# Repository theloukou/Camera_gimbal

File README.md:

# 2-axis Camera Gimbal
Arduino-based 2-axis BLDC gimbal controller

This project consists the main study of my Thesis for my Bachelor of Science at the Department of Automation Engineering of the Piraeus University of Applied Sciences.

It is an Arduino Mega2560 based system, that consists of an extention PCB(shield) that acts as a motor driver for BLCD motors, and an interface between the Arduino and its peripheral devices (motor drivers, IMUs, switches, battery).
Microcontroller code is presented, as well as shield schematic/PCB layout/PCB Gerbers. Also, some 3D-Printed parts used around the gimbal frame are presented in STL form.

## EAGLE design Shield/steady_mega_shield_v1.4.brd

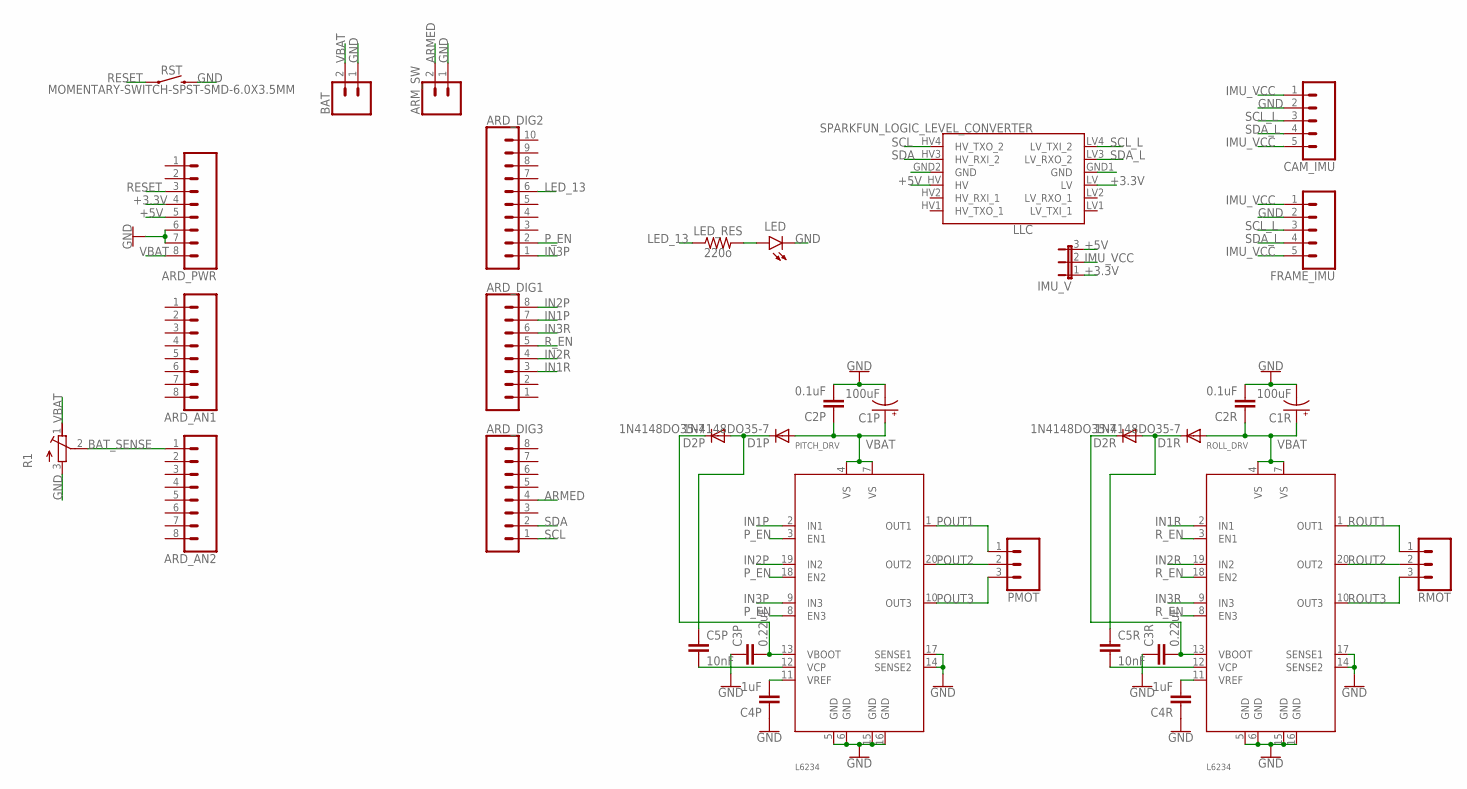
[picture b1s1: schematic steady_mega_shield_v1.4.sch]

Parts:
ARD_AN1, ARD_AN2: CONN_08"; 1X08
ARD_DIG1, ARD_DIG3: CONN_08"; 1X08
ARD_DIG2: CONN_10"; 1X10
ARD_PWR: CONN_08"; 1X08
ARM_SW: CONN_02; 1X02
BAT: CONN_02; 1X02
C1P, C1R: 100uF; CPOL-RADIAL-2.5MM-6.5MM
C2P, C2R: 0.1uF; C025-024X044
C3P, C3R: 0.22uF; C5B2.5
C4P, C4R: 1uF; C5B5.5
C5P, C5R: 10nF; C5B2.5
CAM_IMU: CONN_05JST; JST-5-PTH
D1P, D1R, D2P, D2R: 1N4148DO35-7; DO35-7
FRAME_IMU: CONN_05JST; JST-5-PTH
IMU_V: JP2E; JP2
LED: LED3MM; LED_3MM
LED_RES: 220o; 0805
LLC: SPARKFUN_LOGIC_LEVEL_CONVERTER
PITCH_DRV: L6234; DIL20
PMOT: CONN_03POLAR; MOLEX-1X3
R1: R-TRIMMT93XB; RTRIMT93XB
RMOT: CONN_03POLAR; MOLEX-1X3
ROLL_DRV: L6234; DIL20
RST: MOMENTARY-SWITCH-SPST-SMD-6.0X3.5MM; TACTILE_SWITCH_SMD_6.0X3.5MM

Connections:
+3.3V: ARD_PWR.4, IMU_V.1, LLC.LV
+5V: ARD_PWR.5, IMU_V.3, LLC.HV
ARMED: ARD_DIG3.4, ARM_SW.2
BAT_SENSE: ARD_AN2.1, R1.2 (S)
GND: ARD_PWR.6, ARD_PWR.7, ARM_SW.1, BAT.1, C1P.2 (-), C1R.2 (-), C2P.2, C2R.2, C3P.1, C3R.1, C4P.1, C4R.1, CAM_IMU.2, FRAME_IMU.2, LED.K (C), LLC.GND1 (GND), LLC.GND2 (GND), PITCH_DRV.5 (GND), PITCH_DRV.6 (GND), PITCH_DRV.14 (SENSE2), PITCH_DRV.15 (GND), PITCH_DRV.16 (GND), PITCH_DRV.17 (SENSE1), R1.3 (A), ROLL_DRV.5 (GND), ROLL_DRV.6 (GND), ROLL_DRV.14 (SENSE2), ROLL_DRV.15 (GND), ROLL_DRV.16 (GND), ROLL_DRV.17 (SENSE1), RST.2
IMU_VCC: CAM_IMU.1, CAM_IMU.5, FRAME_IMU.1, FRAME_IMU.5, IMU_V.2
IN1P: ARD_DIG1.7, PITCH_DRV.2 (IN1)
IN1R: ARD_DIG1.3, ROLL_DRV.2 (IN1)
IN2P: ARD_DIG1.8, PITCH_DRV.19 (IN2)
IN2R: ARD_DIG1.4, ROLL_DRV.19 (IN2)
IN3P: ARD_DIG2.1, PITCH_DRV.9 (IN3)
IN3R: ARD_DIG1.6, ROLL_DRV.9 (IN3)
LED_13: ARD_DIG2.6, LED_RES.1
unnamed: C4R.2, ROLL_DRV.11 (VREF)
unnamed: C4P.2, PITCH_DRV.11 (VREF)
unnamed: C5R.2, ROLL_DRV.12 (VCP)
unnamed: C3R.2, D2R.C, ROLL_DRV.13 (VBOOT)
unnamed: C5P.2, PITCH_DRV.12 (VCP)
unnamed: C3P.2, D2P.C, PITCH_DRV.13 (VBOOT)
unnamed: LED.A, LED_RES.2
unnamed: C5P.1, D1P.C, D2P.A
unnamed: C5R.1, D1R.C, D2R.A
POUT1: PITCH_DRV.1 (OUT1), PMOT.1
POUT2: PITCH_DRV.20 (OUT2), PMOT.2
POUT3: PITCH_DRV.10 (OUT3), PMOT.3
P_EN: ARD_DIG2.2, PITCH_DRV.3 (EN1), PITCH_DRV.8 (EN3), PITCH_DRV.18 (EN2)
RESET: ARD_PWR.3, RST.1
ROUT1: RMOT.1, ROLL_DRV.1 (OUT1)
ROUT2: RMOT.2, ROLL_DRV.20 (OUT2)
ROUT3: RMOT.3, ROLL_DRV.10 (OUT3)
R_EN: ARD_DIG1.5, ROLL_DRV.3 (EN1), ROLL_DRV.8 (EN3), ROLL_DRV.18 (EN2)
SCL: ARD_DIG3.1, LLC.HV4 (HV_TXO_2)
SCL_L: CAM_IMU.3, FRAME_IMU.3, LLC.LV4 (LV_TXI_2)
SDA: ARD_DIG3.2, LLC.HV3 (HV_RXI_2)
SDA_L: CAM_IMU.4, FRAME_IMU.4, LLC.LV3 (LV_RXO_2)
VBAT: ARD_PWR.8, BAT.2, C1P.1 (+), C1R.1 (+), C2P.1, C2R.1, D1P.A, D1R.A, PITCH_DRV.4 (VS), PITCH_DRV.7 (VS), R1.1 (E), ROLL_DRV.4 (VS), ROLL_DRV.7 (VS)

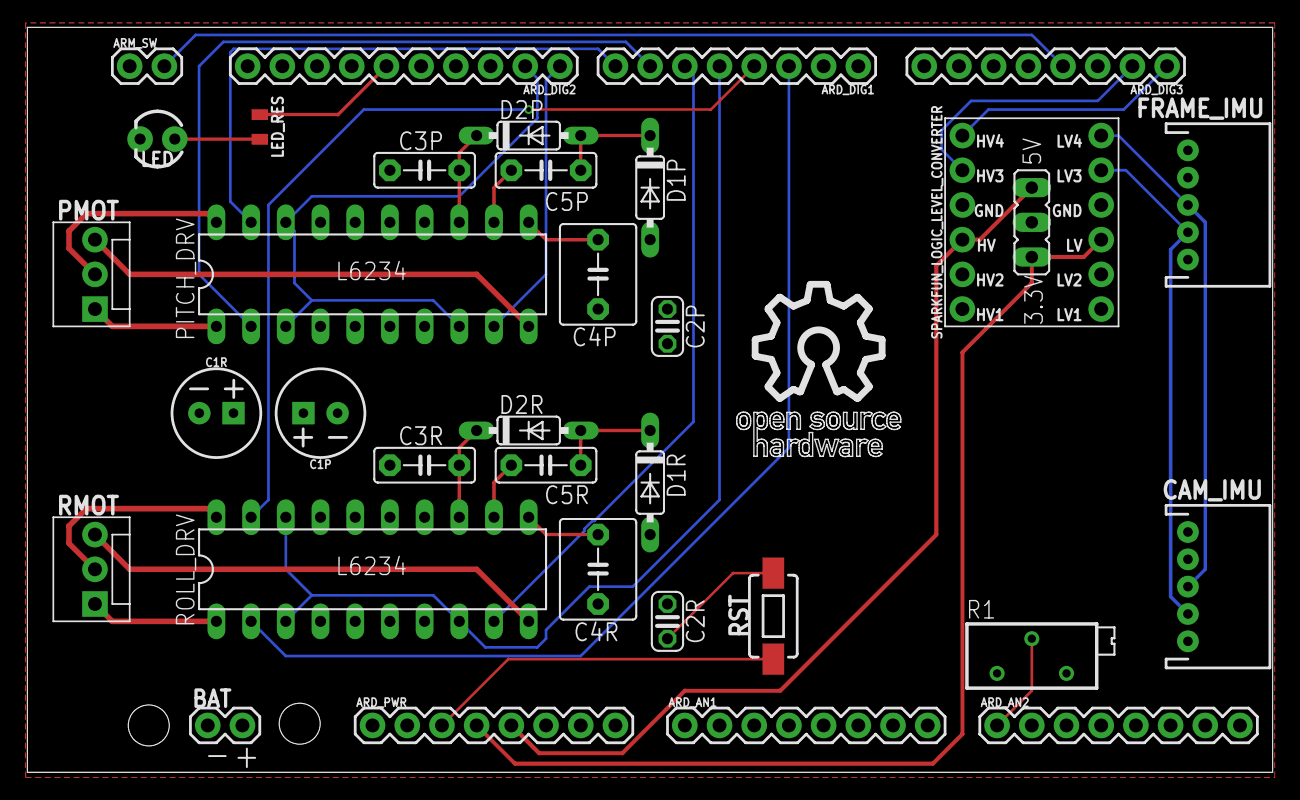
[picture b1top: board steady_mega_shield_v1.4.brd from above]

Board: 4 copper layers, 91.2 x 54.5 mm, 34 parts (0 on the bottom side), 36 nets.

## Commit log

2022-11-20 Added gimbal calibration helper/data visualizer
2022-11-20 Switched to discrete PID, updates for json serial output, support for helper utility

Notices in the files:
parts and their libraries:
SparkFun-Connectors: Licensing: Creative Commons ShareAlike 4.0 International - https://creativecommons.org/licenses/by-sa/4.0
